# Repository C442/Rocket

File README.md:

Rocket 2025
======

Welcome to our latest Project: a rocket guidance system. 

This project took around half a year to build, the other part of the year was spent documenting it. It was originally aimed to improve larger project management under time pressure and university schedule. We wanted to do this project a few years ago already, but somehow ended up with other side quests to fulfill, so this can be seen as our last highschool project, marking a waypoint for bigger, badder and more complex projects. I almost forgot that this project was also supposed to "cure problems related to boredom" and I want to point out that it definitely managed to fill quite some hours...maybe a few too many? Nah...this was worth it. 

This repo will only serve as a project overview and memory. This encompasses the code, the prints, the project paper and most importantly: some pictures 

Table of Content
================

<!--ts-->
- [Visual Designs](#Visual-Designs)
- [Board Computer](#Board-Computer)
- [Parachute Deployment](#Parachute-Deployment)
- [Thrust Vector Control System](#TVC-System)
- [About us](#About-us)
<!--te-->

Visual Designs
==============

Board Computer
==============

Parachute Deployment
====================

TVC System
==========

References
==========

1. [Collins Dictionary – Rocketry](https://www.collinsdictionary.com/dictionary/english/rocketry)  
   Accessed 12 January 2026.

2. [YouTube Video – Our first rocket launch](https://www.youtube.com/watch?v=nfHlhmoQnFs)  
   Accessed 27 January 2026.

3. [Luxembourg Space Agency – Spacewatch Global Article](https://spacewatch.global/2018/09/luxembourg-space-agency-open-for-business-as-new-space-hub/)  
   Accessed 28 January 2026.

4. [BBC News – Rocket Article](https://www.bbc.com/news/articles/cjewvpkw7weo)

5. [NASA Rockets Educator Guide](https://www.nasa.gov/wp-content/uploads/2012/07/rockets-educator-guide-20.pdf)  
   Accessed 28 January 2026.

6. [Wikipedia – Booster (Rocketry)](https://en.wikipedia.org/wiki/Booster_(rocketry))  
   Accessed 28 January 2026.

7. [BBC Science & Environment – Rocket Article](https://www.bbc.com/news/science-environment-24331860)  
   Accessed 28 January 2026.

8. [Eurocircuits – PCB Manufacturing](https://www.eurocircuits.com/)  
   Accessed 2 February 2026.

9. [Printables – Rocket Thrust Vector Control Gimbal](https://www.printables.com/model/9920-k-9-rocket-thrust-vector-control-gimbal-v8/related?lang=de)  
   Accessed 2 February 2026.

10. [YouTube – Nicola Gaiani](https://www.youtube.com/@nicola_gaiani)  
    Accessed 2 February 2026.

11. [Springer – Technische Mechanik Buch](https://link.springer.com/book/10.1007/978-3-662-59886-3)  
    p. 290. Accessed 9 February 2026.

12. [Wikipedia – PID Controller](https://en.wikipedia.org/wiki/Proportional%E2%80%93integral%E2%80%93derivative_controller)  
    Accessed 28 January 2026.

13. [YouTube – Parachute Ejection Inspiration](https://www.youtube.com/watch?v=COkh5ykzC3Y)  
    Accessed 9 February 2026.

14. [Madgwick Filter Explanation](https://medium.com/@k66115704/imu-madgwick-filter-explanation-556fbe7f02e3)  
    Accessed 9 February 2026.

15. [Introduction to Quaternions](https://lisyarus.github.io/blog/posts/introduction-to-quaternions.html)  
    Accessed 9 February 2026.

16. [YouTube – Moto Moto Song](https://www.youtube.com/watch?v=vx5vpG6jEXI)  
    Accessed 9 February 2026.

17. ChatGPT was used to check the text and correct it. In the abstract it was used to rephrase. It was also used to generate code.

18. [Project GitHub Repository](https://github.com/C442/Rocket)  
    The repository designated to this project.

About us
========

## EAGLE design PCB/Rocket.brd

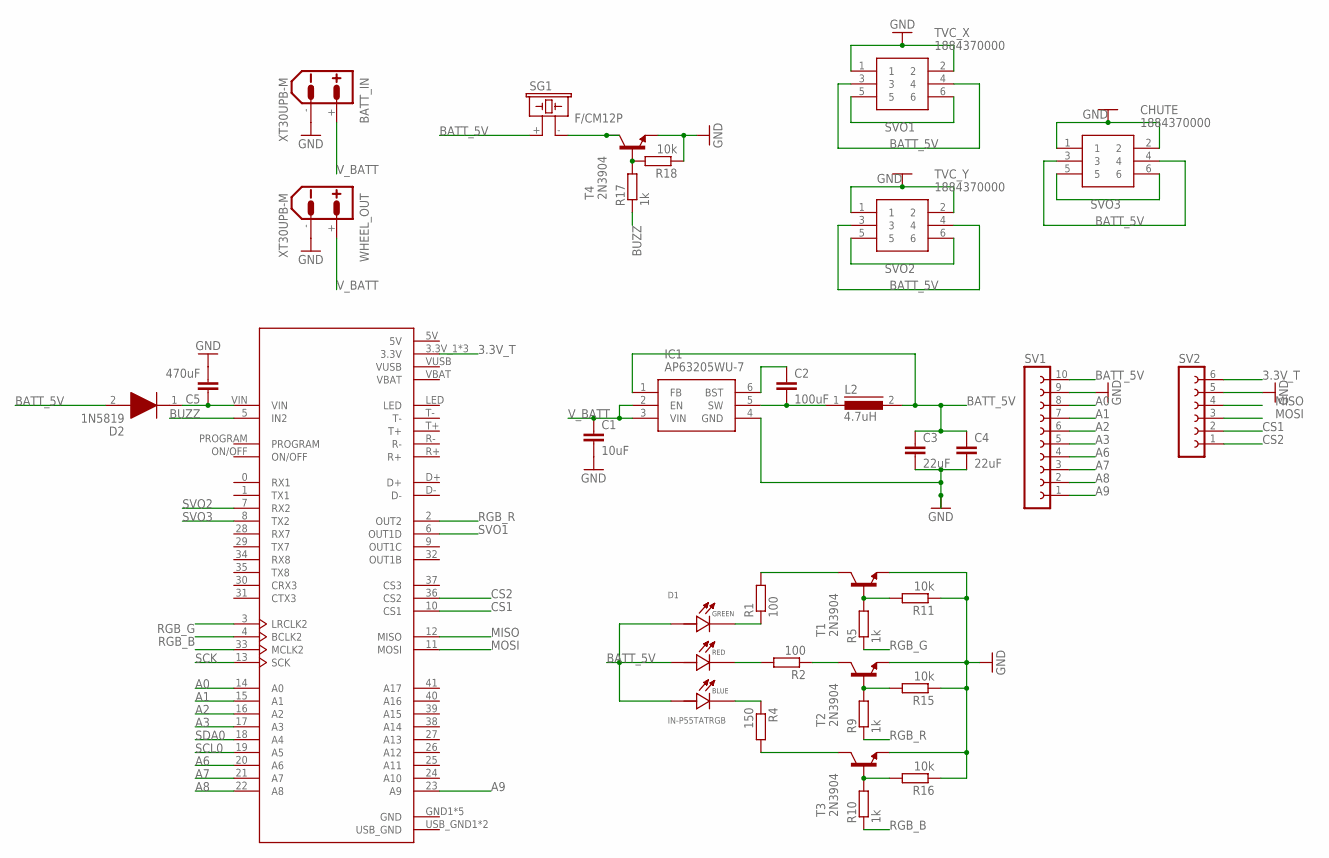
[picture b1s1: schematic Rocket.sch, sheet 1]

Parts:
BATT_IN: XT30UPB-M
C1: 10uF; C2.5-2
C2: 100uF; C2.5-2
C3, C4: 22uF; C2.5-2
C5: 470uF; C2.5-2
CHUTE: 1884370000
D1: IN-P55TATRGB; LED_IN-P55TATRGB
D2: 1N5819; DIOAD1414W86L464D238
IC1: AP63205WU-7; AP63205WU7
L2: 4.7uH; MCC10
R1, R2: 100; 0204/7
R4: 150; 0204/7
R5, R9, R10, R17: 1k; 0204/7
R11, R15, R16, R18: 10k; 0204/7
SG1: F/CM12P
SV1: FE10-1; FE10
SV2: FE06-1; FE06
T1, T2, T3, T4: 2N3904; TO92
TVC_X: 1884370000
TVC_Y: 1884370000
U6: DEV-16771; MODULE_DEV-16771
WHEEL_OUT: XT30UPB-M

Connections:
3.3V_T: SV2.6, U6.3.3V_1 (3.3V), U6.3.3V_2 (3.3V), U6.3.3V_3 (3.3V); also elsewhere on the board
5V: U6.5V
A0: SV1.8, U6.14 (A0)
A1: SV1.7, U6.15 (A1)
A2: SV1.6, U6.16 (A2)
A3: SV1.5, U6.17 (A3)
A6: SV1.4, U6.20 (A6)
A7: SV1.3, U6.21 (A7)
A8: SV1.2, U6.22 (A8)
A9: SV1.1, U6.23 (A9)
BATT_5V: C3.1, C4.1, CHUTE.3, CHUTE.4, D1.4 (G_A), D1.5 (R_A), D1.6 (B_A), D2.2 (A), IC1.1 (FB), L2.2, SG1.+ (1), SV1.10, TVC_X.3, TVC_X.4, TVC_Y.3, TVC_Y.4
BUZZ: R17.1, U6.5 (IN2)
CS1: SV2.2, U6.10 (CS1)
CS2: SV2.1, U6.36 (CS2)
GND: BATT_IN.-, C1.2, C3.2, C4.2, C5.2, CHUTE.1, CHUTE.2, IC1.4 (GND), R11.1, R15.1, R16.1, R18.1, SV1.9, SV2.5, T1.3 (E), T2.3 (E), T3.3 (E), T4.3 (E), TVC_X.1, TVC_X.2, TVC_Y.1, TVC_Y.2, U6.GND1 (GND), U6.GND2 (GND), U6.GND3 (GND), U6.GND4 (GND), U6.GND5 (GND), WHEEL_OUT.-; also elsewhere on the board
MISO: SV2.4, U6.12 (MISO)
MOSI: SV2.3, U6.11 (MOSI)
unnamed: D1.3 (G_C), R1.1
unnamed: D1.2 (R_C), R2.2
unnamed: C5.1, D2.1 (K), U6.VIN
unnamed: D1.1 (B_C), R4.1
unnamed: R1.2, T1.1 (C)
unnamed: C2.2, IC1.5 (SW), L2.1
unnamed: C2.1, IC1.6 (BST)
unnamed: R2.1, T2.1 (C)
unnamed: R4.2, T3.1 (C)
unnamed: R5.2, R11.2, T1.2 (B)
unnamed: R9.2, R15.2, T2.2 (B)
unnamed: R10.2, R16.2, T3.2 (B)
unnamed: SG1.- (2), T4.1 (C)
unnamed: R17.2, R18.2, T4.2 (B)
RGB_B: R10.1, U6.4 (BCLK2)
RGB_G: R5.1, U6.3 (LRCLK2)
RGB_R: R9.1, U6.2 (OUT2)
SCK: U6.13 (SCK)
SCL0: U6.19 (A5); also elsewhere on the board
SDA0: U6.18 (A4); also elsewhere on the board
SVO1: TVC_X.5, TVC_X.6, U6.6 (OUT1D)
SVO2: TVC_Y.5, TVC_Y.6, U6.7 (RX2)
SVO3: CHUTE.5, CHUTE.6, U6.8 (TX2)
USB_GND: U6.USB_GND1 (USB_GND), U6.USB_GND2 (USB_GND)
V_BATT: BATT_IN.+, C1.1, IC1.2 (EN), IC1.3 (VIN), WHEEL_OUT.+

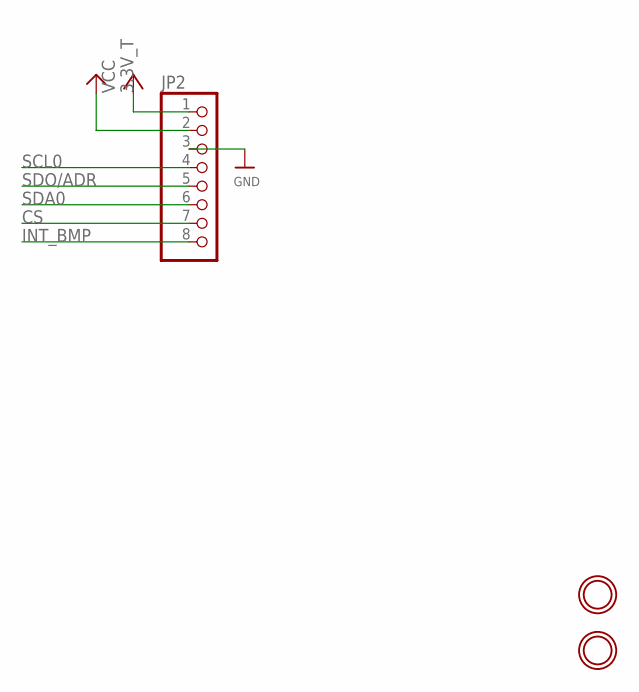
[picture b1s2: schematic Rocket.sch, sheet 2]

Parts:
JP2: HEADER-1X870MIL; 1X08_ROUND_70
U$24, U$26: MOUNTINGHOLE2.5; MOUNTINGHOLE_2.5_PLATED

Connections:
3.3V_BMP: JP2.2
3.3V_T: JP2.1; also elsewhere on the board
CS: JP2.7
GND: JP2.3; also elsewhere on the board
INT_BMP: JP2.8
SCL0: JP2.4; also elsewhere on the board
SDA0: JP2.6; also elsewhere on the board
SDO/ADR: JP2.5

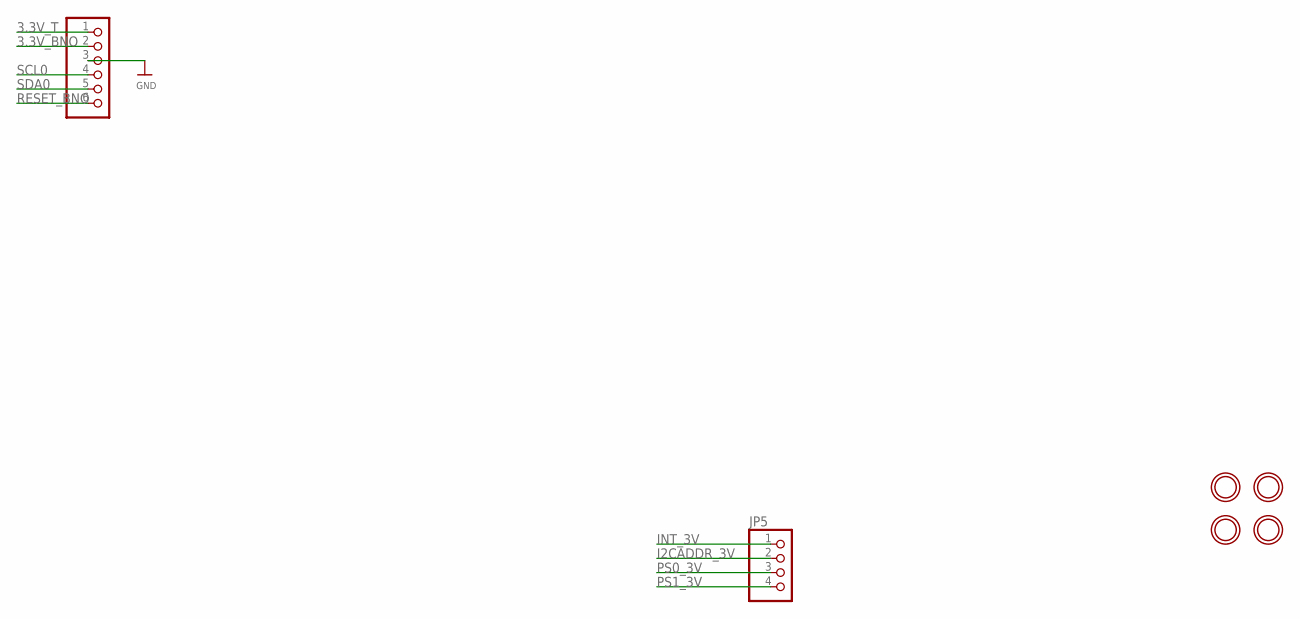
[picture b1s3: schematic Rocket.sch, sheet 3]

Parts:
JP5: HEADER-1X476MIL; 1X04_ROUND_76
JP6: HEADER-1X670MIL; 1X06_ROUND_70
U$109, U$110, U$112, U$113: MOUNTINGHOLE2.5; MOUNTINGHOLE_2.5_PLATED

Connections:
3.3V_BNO: JP6.2
3.3V_T: JP6.1; also elsewhere on the board
GND: JP6.3; also elsewhere on the board
I2CADDR_3V: JP5.2
INT_3V: JP5.1
PS0_3V: JP5.3
PS1_3V: JP5.4
RESET_BNO: JP6.6
SCL0: JP6.4; also elsewhere on the board
SDA0: JP6.5; also elsewhere on the board

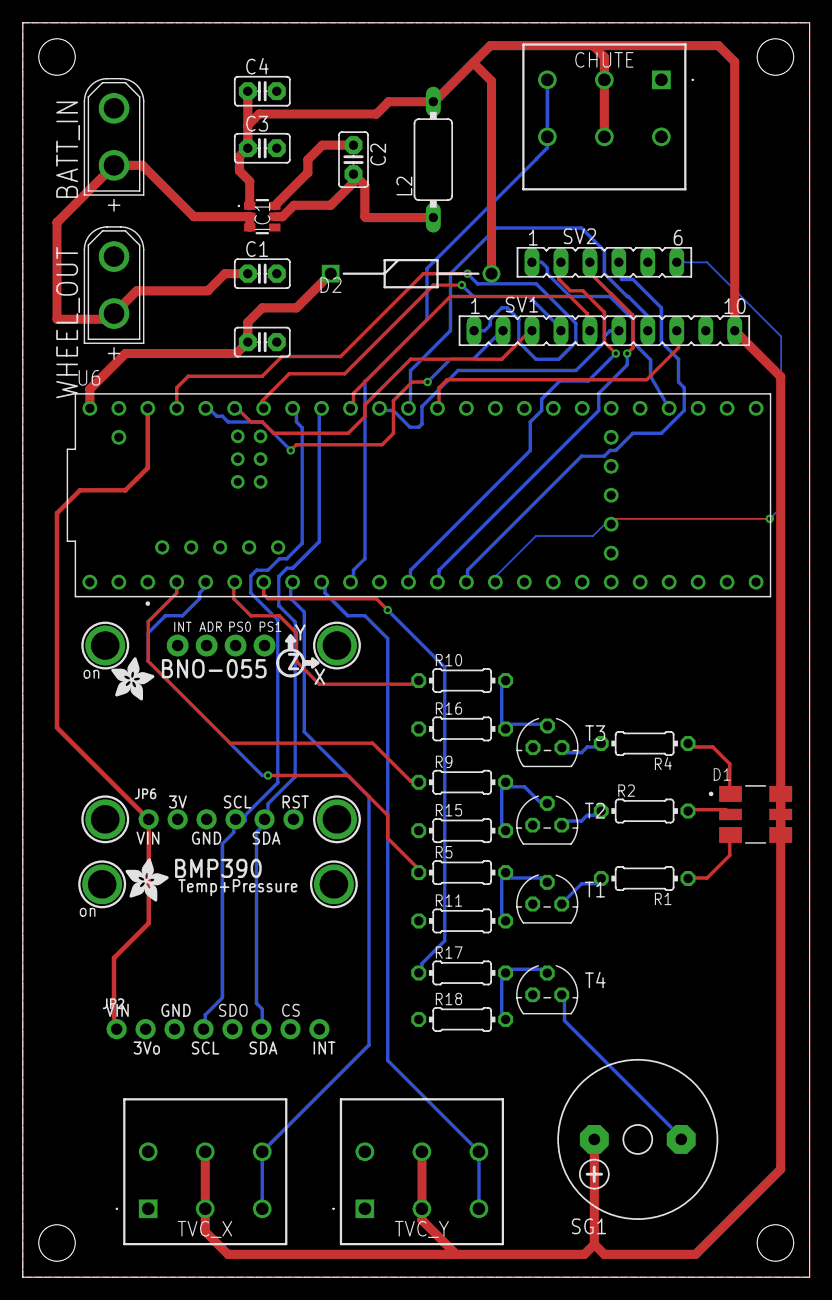
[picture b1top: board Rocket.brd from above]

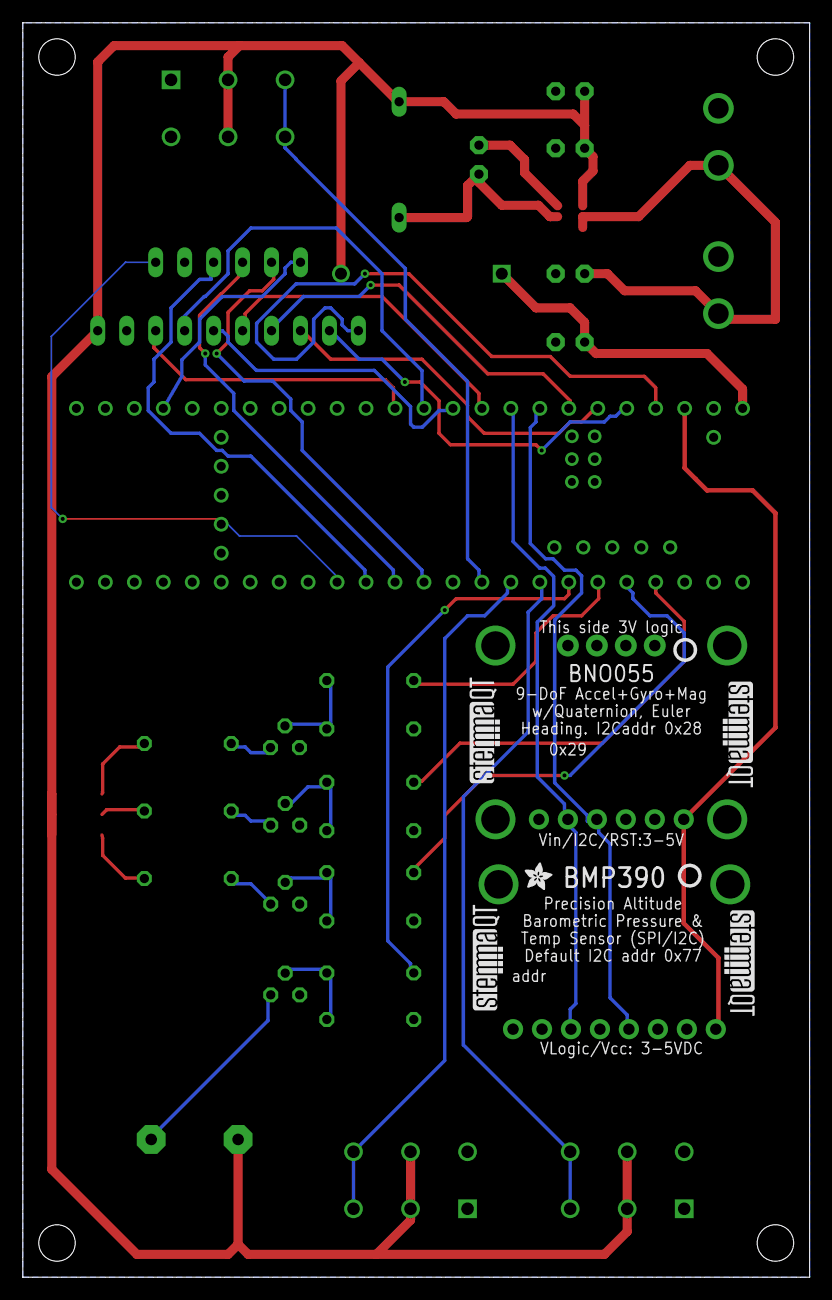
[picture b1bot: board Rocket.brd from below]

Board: 2 copper layers, 69.0 x 110.0 mm, 51 parts (7 on the bottom side), 40 nets.

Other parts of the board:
U$32: ADAFRUIT_2.5MM
U$39, U$117: ADAFRUIT_3.5MM
U$43, U$118: PCBFEAT-REV-040
U$44, U$50, U$119, U$120: STEMMAQT

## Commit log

2025-02-27 Initialising repo
2025-02-27 Fixing ordners
2025-02-27 adding sketches
2025-02-27 Update README.md
    Little visual update
    Next:
    make table of contents link to headers
    make headers link to respective directories
2025-03-20 pulling code from laptop to raspy- camera tryout
2025-03-20 semi-simultaneous camera(picture) usage
2025-03-21 simultaneous shell scripted image taking with 2 cams
2025-03-22 name changing
2025-03-26 Add files via upload
    Nose cone with chute release mechanism
2025-03-27 Put my files in Deployment Mechanism
2025-03-27 All my other file for the nose cone
2025-03-28 Short/Easy Code for Parachute Deployment
2025-04-25 Loading up the TVC 3D Files
2025-04-25 Final version of the nose cone cap / base(Forget all the other)
2025-04-25 Uploaded 3D files of the reaction wheel
2025-04-25 My first PID Controller for the TVC
2025-04-25 Just a TVC picture
2025-04-25 A quick demo of the chute deployment
2025-04-25 Screenshot of the board computer (designed in Eagle)
2025-05-10 cleaning up via raspy terminal
2025-05-12 night shift be over
2025-05-25 Probably final design of the rocket PCB / Gerber Files
2025-05-25 Small changes on the PCB
2025-05-25 Removed old Gerber Files
2026-02-22 Uploaded all relevant files for our project
2026-02-22 Deleted some files
2026-02-23 Final touches of the repo
2026-02-23 adding video thumbnail
2026-02-23 Revise README with new project title and introduction
    Updated project title and improved welcome message.
2026-03-16 Adding project paper
